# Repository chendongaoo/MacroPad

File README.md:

# MacroPad
A 6 key and 1 rotary encoder macropad designed so I can learn pcbs.

This was my first time ever doing a hardware project involving PCBs so I would say this was a really educational and fun experience!

# CAD Model
The case of the macropad was built through AutoDesk Inventor

# PCB
I used KiCAD for the pcb design and also the schematics.

- Schematic
- 
- PCB Design
- 

# Firmware
QMK Firmware was used in order to make the firmware of the macropad. I was able to let it have my 6 keys type different letters out and also have the rotary encoder be for volume.

# BOM (Bill of Materials)
|Quantity|Item|Link|
|---|---|---|
|1|Seeed XIAO RP2040|https://www.seeedstudio.com/XIAO-RP2040-v1-0-p-5026.html?srsltid=AfmBOoqp9hTYIDmiRi8G-t43GNcj0WLZ4-Bl1FHT_aNiL9EnoWQGMEwN|
|1|EC11 Rotary Encoder|https://keeb.io/products/rotary-encoder-ec11?srsltid=AfmBOopjsudrm_2NT5rApQGzpvWgGaP1affFDQzp-gO6didcxRWisLA-|
|4|M3x16mm Screws|https://www.homedepot.com/p/Hillman-M3-0-5-x-16-mm-Internal-Hex-Button-Head-Cap-Screws-16-Pack-44458/204801177?source=shoppingads&locale=en-US&fp=ggl&srsltid=AfmBOooD-jeBspxgD6yZUO5bHkrZNxwbnfEfS0LIUxeRf3vvWrbXQBDLLQk|
|6|MX-Style Switches|https://www.gateron.co/collections/mx-switches/products/gateron-switch-set|
|6|White Blank DSA Keycaps|https://www.adafruit.com/product/4998?srsltid=AfmBOoqWXq0PUuXsWHtaNkMeOQ-MZJd006PQ38bVfjTifiNstVszIAVgm1U|
|PCB Estimated Price|$2.10|

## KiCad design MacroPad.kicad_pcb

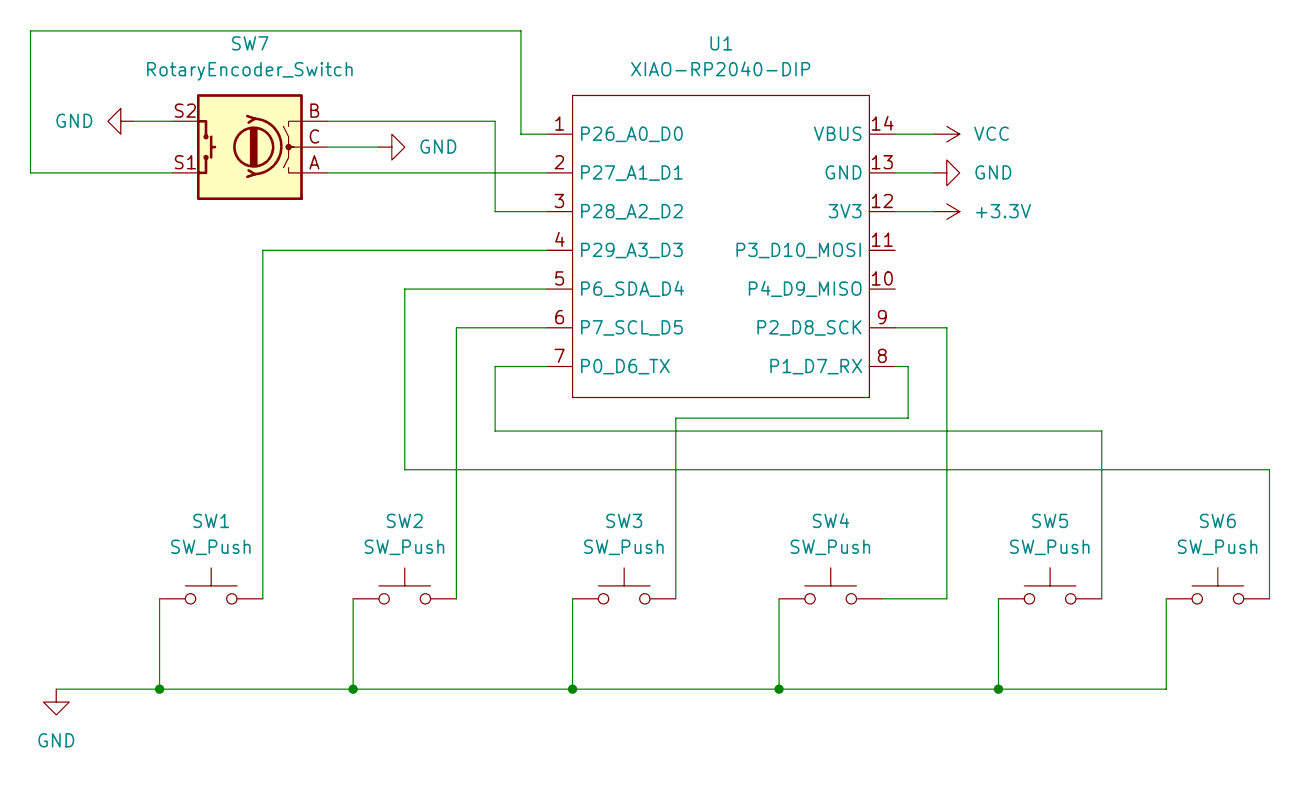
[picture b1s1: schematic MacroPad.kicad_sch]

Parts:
SW1, SW2, SW3, SW4, SW5, SW6: SW_Push; SW_Cherry_MX_1.00u_PCB
SW7: RotaryEncoder_Switch; RotaryEncoder_Alps_EC11E-Switch_Vertical_H20mm
U1: XIAO-RP2040-DIP

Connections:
+3.3V: U1.12 (3V3)
GND: SW1.1, SW2.1, SW3.1, SW4.1, SW5.1, SW6.1, SW7.C, SW7.S2, U1.13 (GND)
unnamed: SW5.2, U1.7 (P0_D6_TX)
unnamed: SW3.2, U1.8 (P1_D7_RX)
unnamed: SW4.2, U1.9 (P2_D8_SCK)
unnamed: SW6.2, U1.5 (P6_SDA_D4)
unnamed: SW2.2, U1.6 (P7_SCL_D5)
unnamed: SW7.S1, U1.1 (P26_A0_D0)
unnamed: SW7.A, U1.2 (P27_A1_D1)
unnamed: SW7.B, U1.3 (P28_A2_D2)
unnamed: SW1.2, U1.4 (P29_A3_D3)
VCC: U1.14 (VBUS)

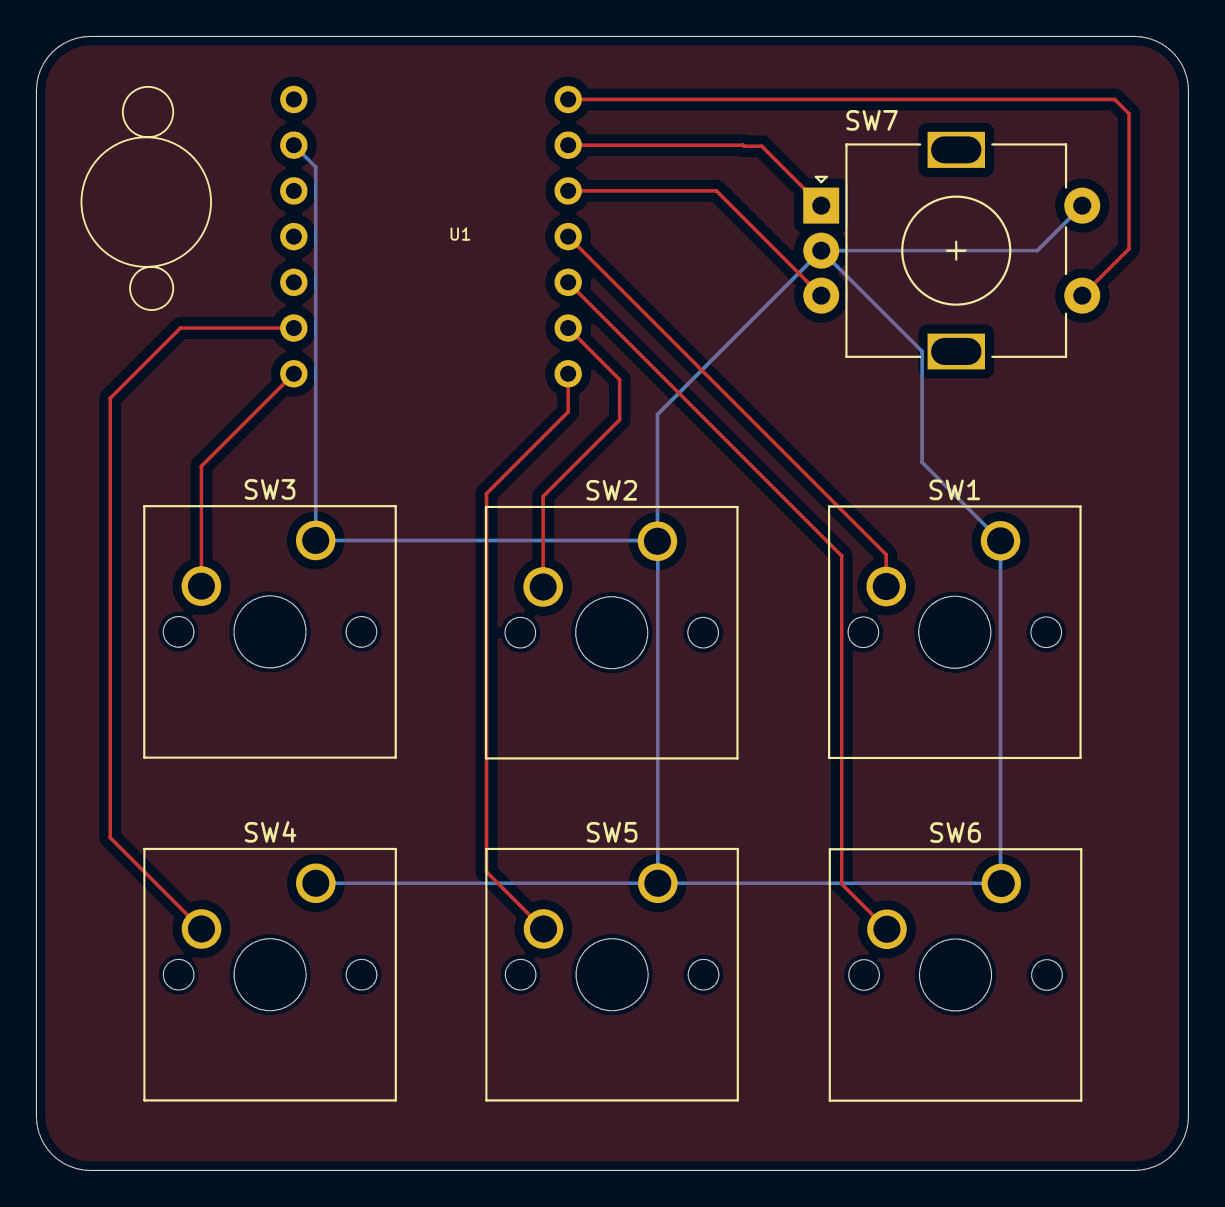
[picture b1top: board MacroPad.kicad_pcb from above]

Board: 2 copper layers, 64.0 x 63.0 mm, 8 parts (1 on the bottom side), 10 nets.

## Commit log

2026-04-28 added files for project
2026-04-28 added firmware
2026-04-28 reorganizing files
2026-04-28 added BOM
